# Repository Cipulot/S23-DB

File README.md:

# S23 DB

S23 daughterboard with CC resistors.

There's not much to be said about this board. It's a daughterboard for the S23 by Sho, with the CC resistors to allow full USB-C operations.

The original JST ZH/ZR connector is replaced with one that has horizontal mount anchor points, to avoid mechanical stress on the connector (LCSC part number C485354).

The pinout is marked on the bottom of the PCB for reference.

## License

<br />This work is licensed under a <a rel="license" href="http://creativecommons.org/licenses/by-nc-sa/4.0/">Creative Commons Attribution-NonCommercial-ShareAlike 4.0 International License</a>.

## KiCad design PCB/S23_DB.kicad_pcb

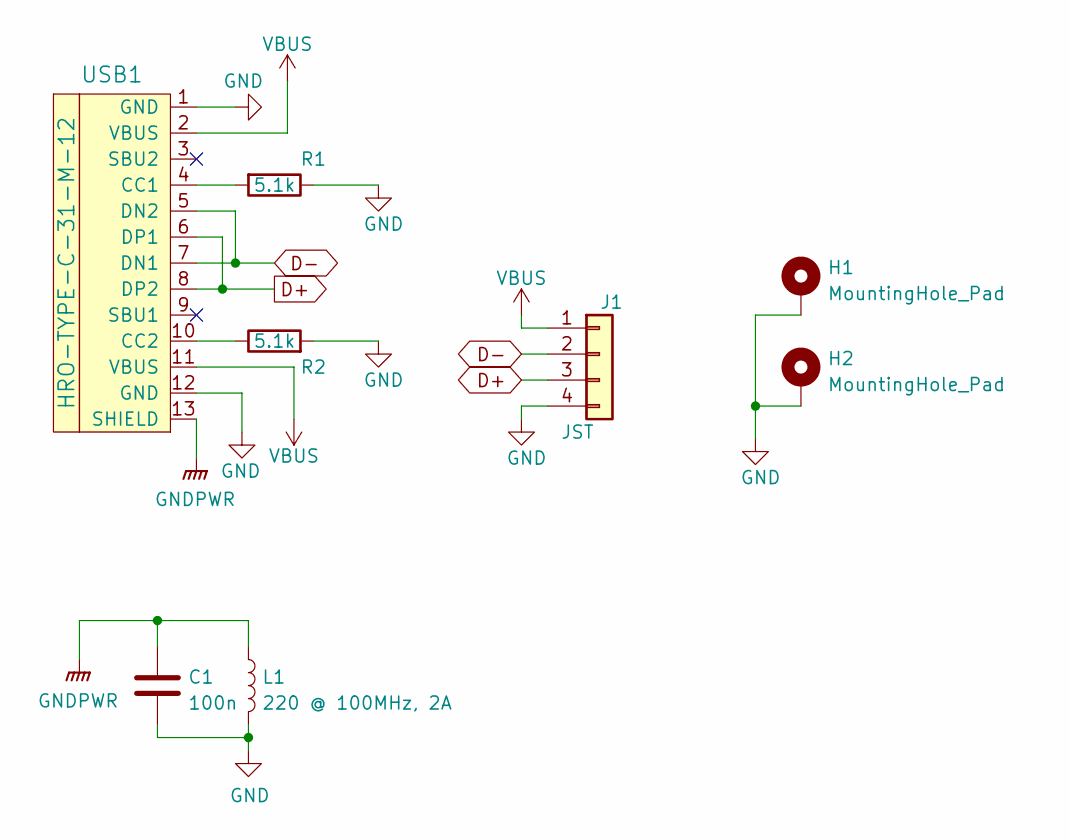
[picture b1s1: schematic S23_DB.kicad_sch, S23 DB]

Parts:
C1: 100n; C_0402_1005Metric; LCSC C307331
H1, H2: MountingHole_Pad; MountingHole_2.2mm_M2_ISO7380_Pad
J1: JST; JST_S4B-ZR-SM4A-TF(LF)(SN); MPN S4B-ZR-SM4A-TF(LF)(SN); LCSC C485354
L1: 220 @ 100MHz, 2A; L_0603_1608Metric; LCSC C85832
R1, R2: 5.1k; R_0402_1005Metric; LCSC C25905
USB1: HRO-TYPE-C-31-M-12; HRO-TYPE-C-31-M-12-Assembly; LCSC C165948

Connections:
D+: J1.3, USB1.6 (DP1), USB1.8 (DP2)
D-: J1.2, USB1.5 (DN2), USB1.7 (DN1)
GND: C1.2, H1.1, H2.1, J1.4, J1.S1, J1.S2, L1.2, R1.1, R2.2, USB1.1 (GND), USB1.12 (GND)
GNDPWR: C1.1, L1.1, USB1.13 (SHIELD)
unnamed: R1.2, USB1.4 (CC1)
unnamed: R2.1, USB1.10 (CC2)
VBUS: J1.1, USB1.2 (VBUS), USB1.11 (VBUS)

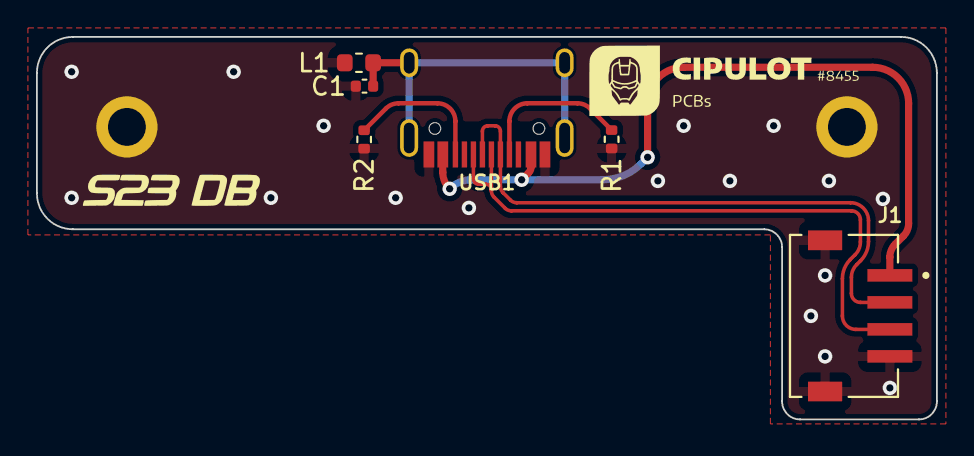
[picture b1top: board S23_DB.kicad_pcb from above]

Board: 2 copper layers, 50.0 x 21.2 mm, 8 parts (0 on the bottom side), 7 nets.

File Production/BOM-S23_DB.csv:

Comment,Designator,Footprint,LCSC
HRO-TYPE-C-31-M-12,USB1,HRO-TYPE-C-31-M-12-Assembly,C165948
5.1k,"R1,R2",R_0402_1005Metric,C25905
100n,C1,C_0402_1005Metric,C307331
JST,J1,JST_S4B-ZR-SM4A-TF(LF)(SN),C485354
"220 @ 100MHz, 2A",L1,L_0603_1608Metric,C85832

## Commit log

2022-12-03 Assets dump
2022-12-03 PCB project dump
2022-12-03 Production files dump
2022-12-03 Update connector part for better availability.
2022-12-05 Fixed silkscreen order for Data lines
2022-12-15 Added STEP model
2023-11-15 Update LICENSE
    Change of License
2023-11-17 Update sheets
2024-03-03 Update
    Updated the License for the project and relative details.

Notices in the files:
PCB/S23_DB.kicad_pcb:
CC-BY-NC-SA-4.0
